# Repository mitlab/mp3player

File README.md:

mp3player
=========

AVR + VS1053 MP3 Decoder + WiFly RN-131 WiFi module

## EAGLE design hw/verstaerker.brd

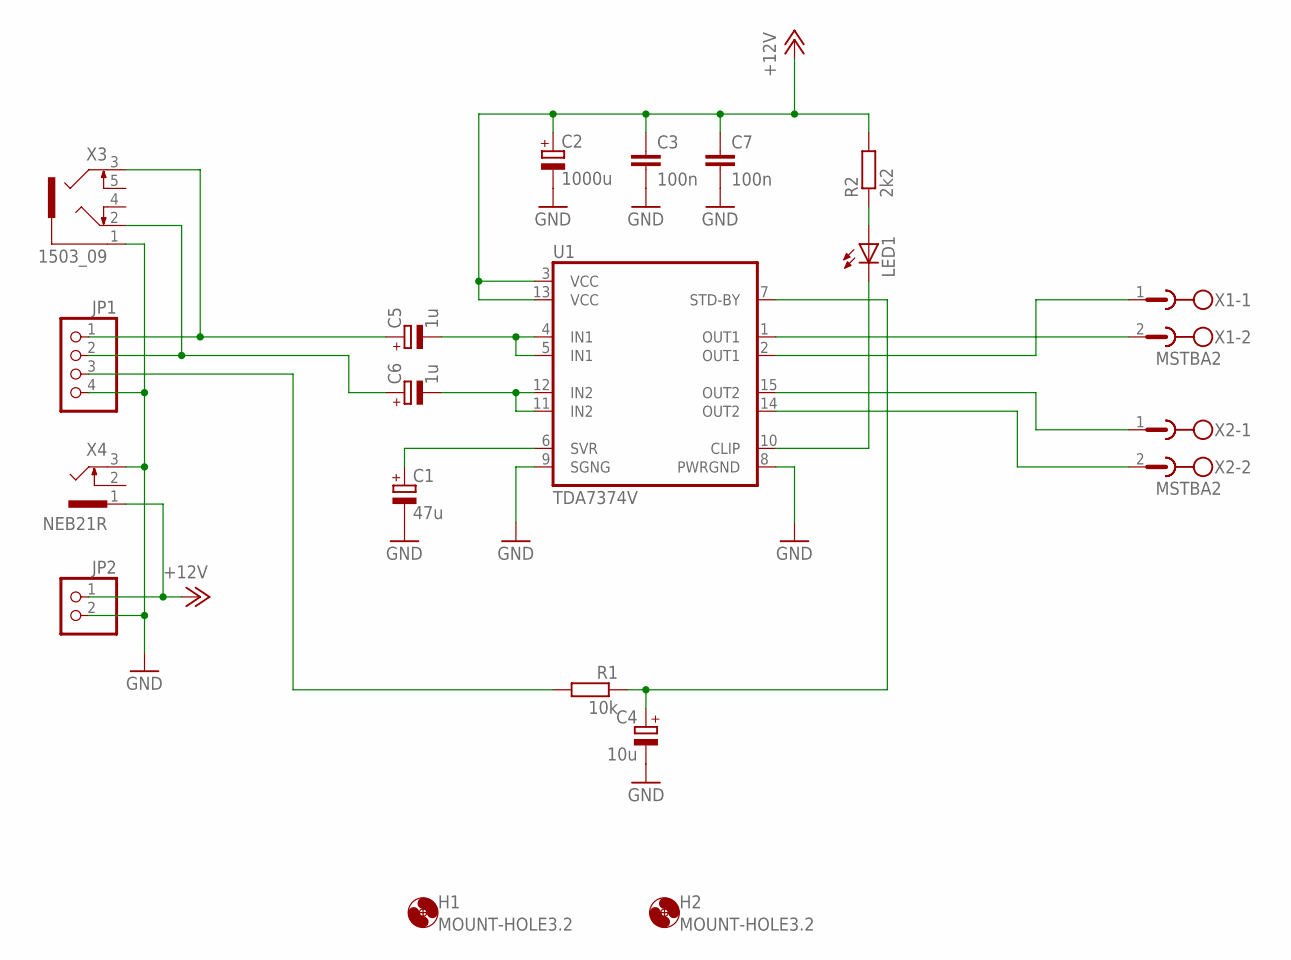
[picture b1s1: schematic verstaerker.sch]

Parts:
C1: 47u; E2,5-7
C2: 1000u; E3,5-8
C3, C7: 100n; C050-025X075
C4: 10u; E2-5
C5, C6: 1u; E2,5-5
H1, H2: MOUNT-HOLE3.2; 3,2
JP1: PINHD-1X4; 1X04
JP2: PINHD-1X2; 1X02
LED1: LED5MM
R1: 10k; R0805
R2: 2k2; R0805
U1: TDA7374V; MULTIWATT-15V
X1, X2: MSTBA2
X3: 1503_09
X4: NEB21R

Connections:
+12V: C2.+, C3.1, C7.1, JP2.1, R2.2, U1.3 (VCC), U1.13 (VCC), X4.1
GND: C1.-, C2.-, C3.2, C4.-, C7.2, JP1.4, JP2.2, U1.8 (PWRGND), U1.9 (SGNG), X3.1, X4.3
unnamed: C1.+, U1.6 (SVR)
unnamed: LED1.K (C), U1.10 (CLIP)
unnamed: C4.+, R1.1, U1.7 (STD-BY)
unnamed: JP1.3, R1.2
unnamed: C5.+, JP1.1, X3.3
unnamed: C6.-, U1.11 (IN2), U1.12 (IN2)
unnamed: LED1.A, R2.1
unnamed: C6.+, JP1.2, X3.2
unnamed: C5.-, U1.4 (IN1), U1.5 (IN1)
unnamed: U1.1 (OUT1), X1.2
unnamed: U1.2 (OUT1), X1.1
unnamed: U1.14 (OUT2), X2.2
unnamed: U1.15 (OUT2), X2.1

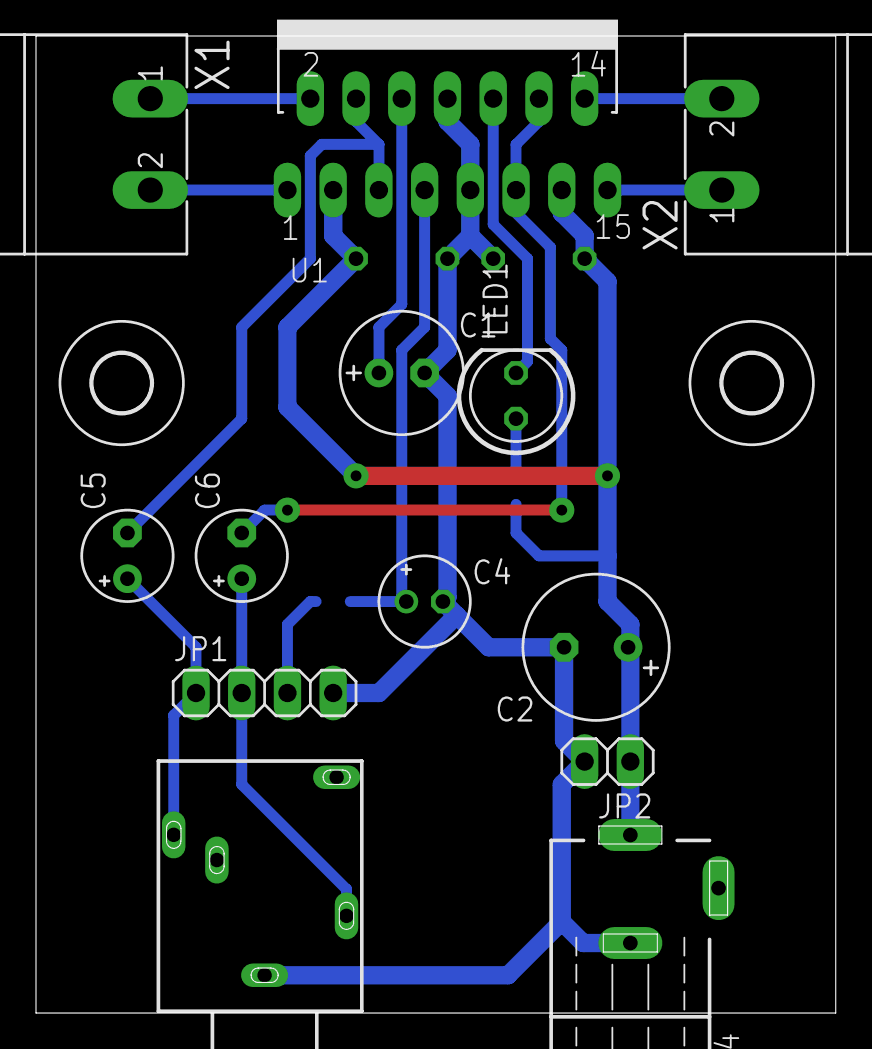
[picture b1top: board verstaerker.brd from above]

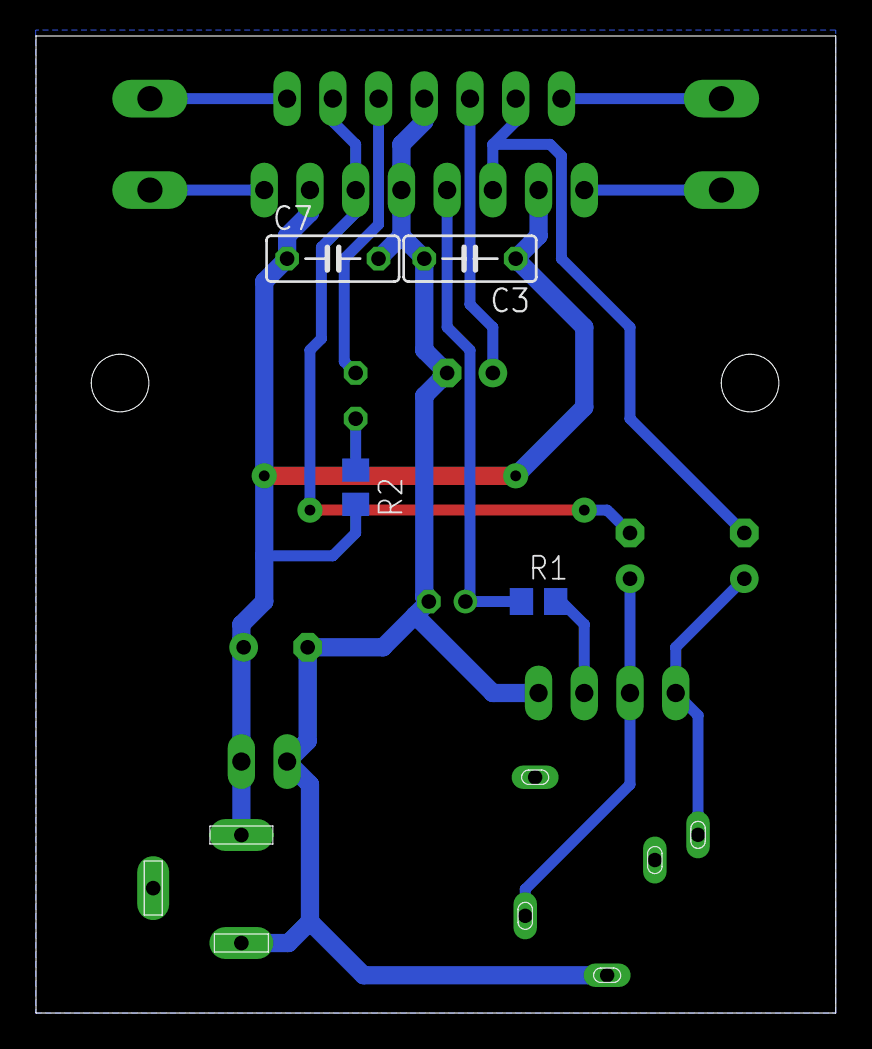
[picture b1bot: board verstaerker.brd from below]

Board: 2 copper layers, 44.4 x 54.3 mm, 19 parts (4 on the bottom side), 15 nets.

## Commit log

2012-09-08 Initial checkin
2012-09-09 Started revising electronics, designed prototype front panel. Mainboard not even half done...
2012-09-09 Provided for 2mm material thickness
